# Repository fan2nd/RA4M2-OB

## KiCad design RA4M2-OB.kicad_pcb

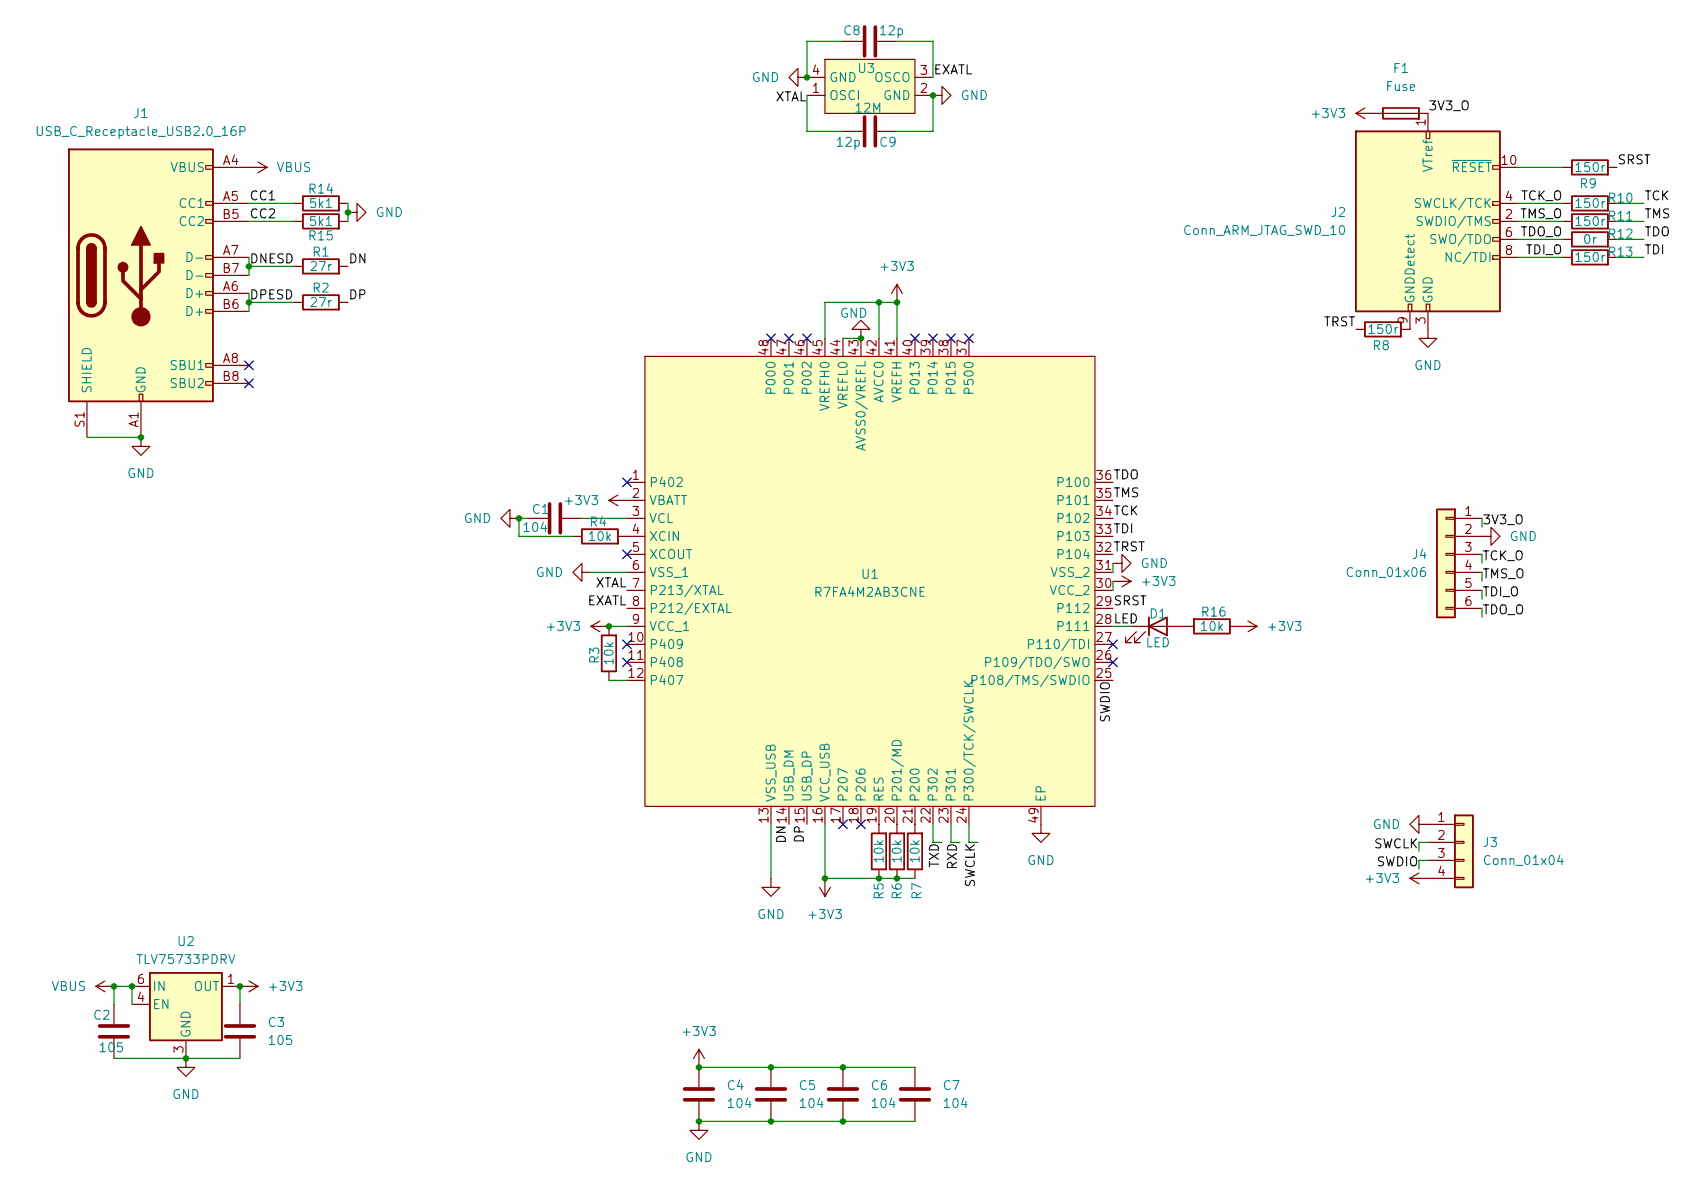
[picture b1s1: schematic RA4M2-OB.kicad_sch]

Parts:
C1, C4, C5, C6, C7: 104; C_0402_1005Metric
C2, C3: 105; C_0402_1005Metric
C8, C9: 12p; C_0402_1005Metric
D1: LED; LED_0402_1005Metric
F1: Fuse; Fuse_0805_2012Metric
J1: USB_C_Receptacle_USB2.0_16P; USB_C_Receptacle_HRO_TYPE-C-31-M-12
J2: Conn_ARM_JTAG_SWD_10; IDC-smd-02x05-1.27
J3: Conn_01x04; PinHeader_1x04_P1.27mm_Vertical
J4: Conn_01x06; PinHeader_1x06_P2.54mm_Horizontal
R1, R2: 27r; R_0402_1005Metric
R3, R4, R5, R6, R7, R16: 10k; R_0402_1005Metric
R8, R9, R10, R11, R13: 150r; R_0402_1005Metric
R12: 0r; R_0402_1005Metric
R14, R15: 5k1; R_0402_1005Metric
U1: R7FA4M2AB3CNE; QFN-48-1EP_7x7mm_P0.5mm_EP5.3x5.3mm
U2: TLV75733PDRV; WSON-6-1EP_2x2mm_P0.65mm_EP1x1.6mm
U3: 12M; Oscillator_SMD_13_3.2x2.5mm

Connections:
+3V3: C3.1, C4.1, C5.1, C6.1, C7.1, F1.1, J3.4, R3.2, R5.1, R6.1, R7.1, R16.1, U1.2 (VBATT), U1.9 (VCC_1), U1.16 (VCC_USB), U1.30 (VCC_2), U1.41 (VREFH), U1.42 (AVCC0), U1.45 (VREFH0), U2.1 (OUT)
/3V3_O: F1.2, J2.1 (VTref), J4.1
/CC1: J1.A5 (CC1), R14.1
/CC2: J1.B5 (CC2), R15.1
/DN: R1.2, U1.14 (USB_DM)
/DNESD: J1.A7 (D-), J1.B7 (D-), R1.1
/DP: R2.2, U1.15 (USB_DP)
/DPESD: J1.A6 (D+), J1.B6 (D+), R2.1
/EXATL: C8.2, U1.8 (P212/EXTAL), U3.3 (OSCO)
/LED: D1.1 (K), U1.28 (P111)
/RXD: U1.23 (P301)
/SRST: R9.2, U1.29 (P112)
/SWCLK: J3.2, U1.24 (P300/TCK/SWCLK)
/SWDIO: J3.3, U1.25 (P108/TMS/SWDIO)
/TCK: R10.2, U1.34 (P102)
/TCK_O: J2.4 (SWCLK/TCK), J4.3, R10.1
/TDI: R13.2, U1.33 (P103)
/TDI_O: J2.8 (NC/TDI), J4.5, R13.1
/TDO: R12.2, U1.36 (P100)
/TDO_O: J2.6 (SWO/TDO), J4.6, R12.1
/TMS: R11.2, U1.35 (P101)
/TMS_O: J2.2 (SWDIO/TMS), J4.4, R11.1
/TRST: R8.1, U1.32 (P104)
/TXD: U1.22 (P302)
/XTAL: C9.1, U1.7 (P213/XTAL), U3.1 (OSCI)
GND: C1.1, C2.2, C3.2, C4.2, C5.2, C6.2, C7.2, C8.1, C9.2, J1.A1 (GND), J1.A12 (GND), J1.B1 (GND), J1.B12 (GND), J1.S1 (SHIELD), J2.3 (GND), J2.5 (GND), J3.1, J4.2, R4.1, R14.2, R15.2, U1.6 (VSS_1), U1.13 (VSS_USB), U1.31 (VSS_2), U1.43 (AVSS0/VREFL), U1.44 (VREFL0), U1.49 (EP), U2.3 (GND), U2.7 (GND), U3.2 (GND), U3.4 (GND)
unnamed: D1.2 (A), R16.2
unnamed: J2.9 (GNDDetect), R8.2
unnamed: J2.10 (~RESET), R9.1
unnamed: R7.2, U1.21 (P200)
unnamed: R6.2, U1.20 (P201/MD)
unnamed: R3.1, U1.12 (P407)
unnamed: R5.2, U1.19 (RES)
unnamed: C1.2, U1.3 (VCL)
unnamed: R4.2, U1.4 (XCIN)
VBUS: C2.1, J1.A4 (VBUS), J1.A9 (VBUS), J1.B4 (VBUS), J1.B9 (VBUS), U2.4 (EN), U2.6 (IN)

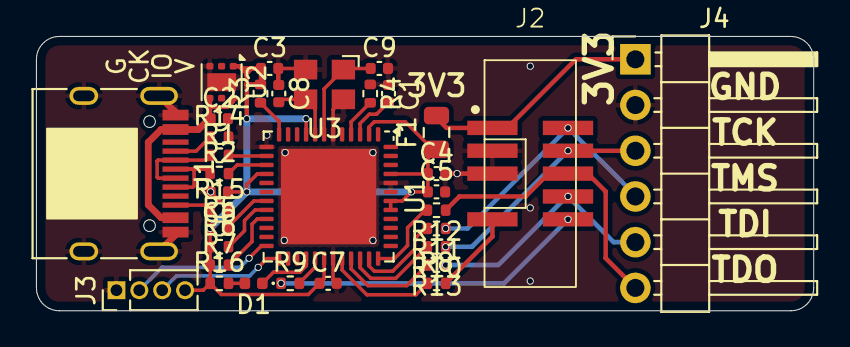
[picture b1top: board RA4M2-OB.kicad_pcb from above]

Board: 2 copper layers, 43.2 x 15.2 mm, 34 parts (0 on the bottom side), 34 nets.

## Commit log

2024-12-30 init
